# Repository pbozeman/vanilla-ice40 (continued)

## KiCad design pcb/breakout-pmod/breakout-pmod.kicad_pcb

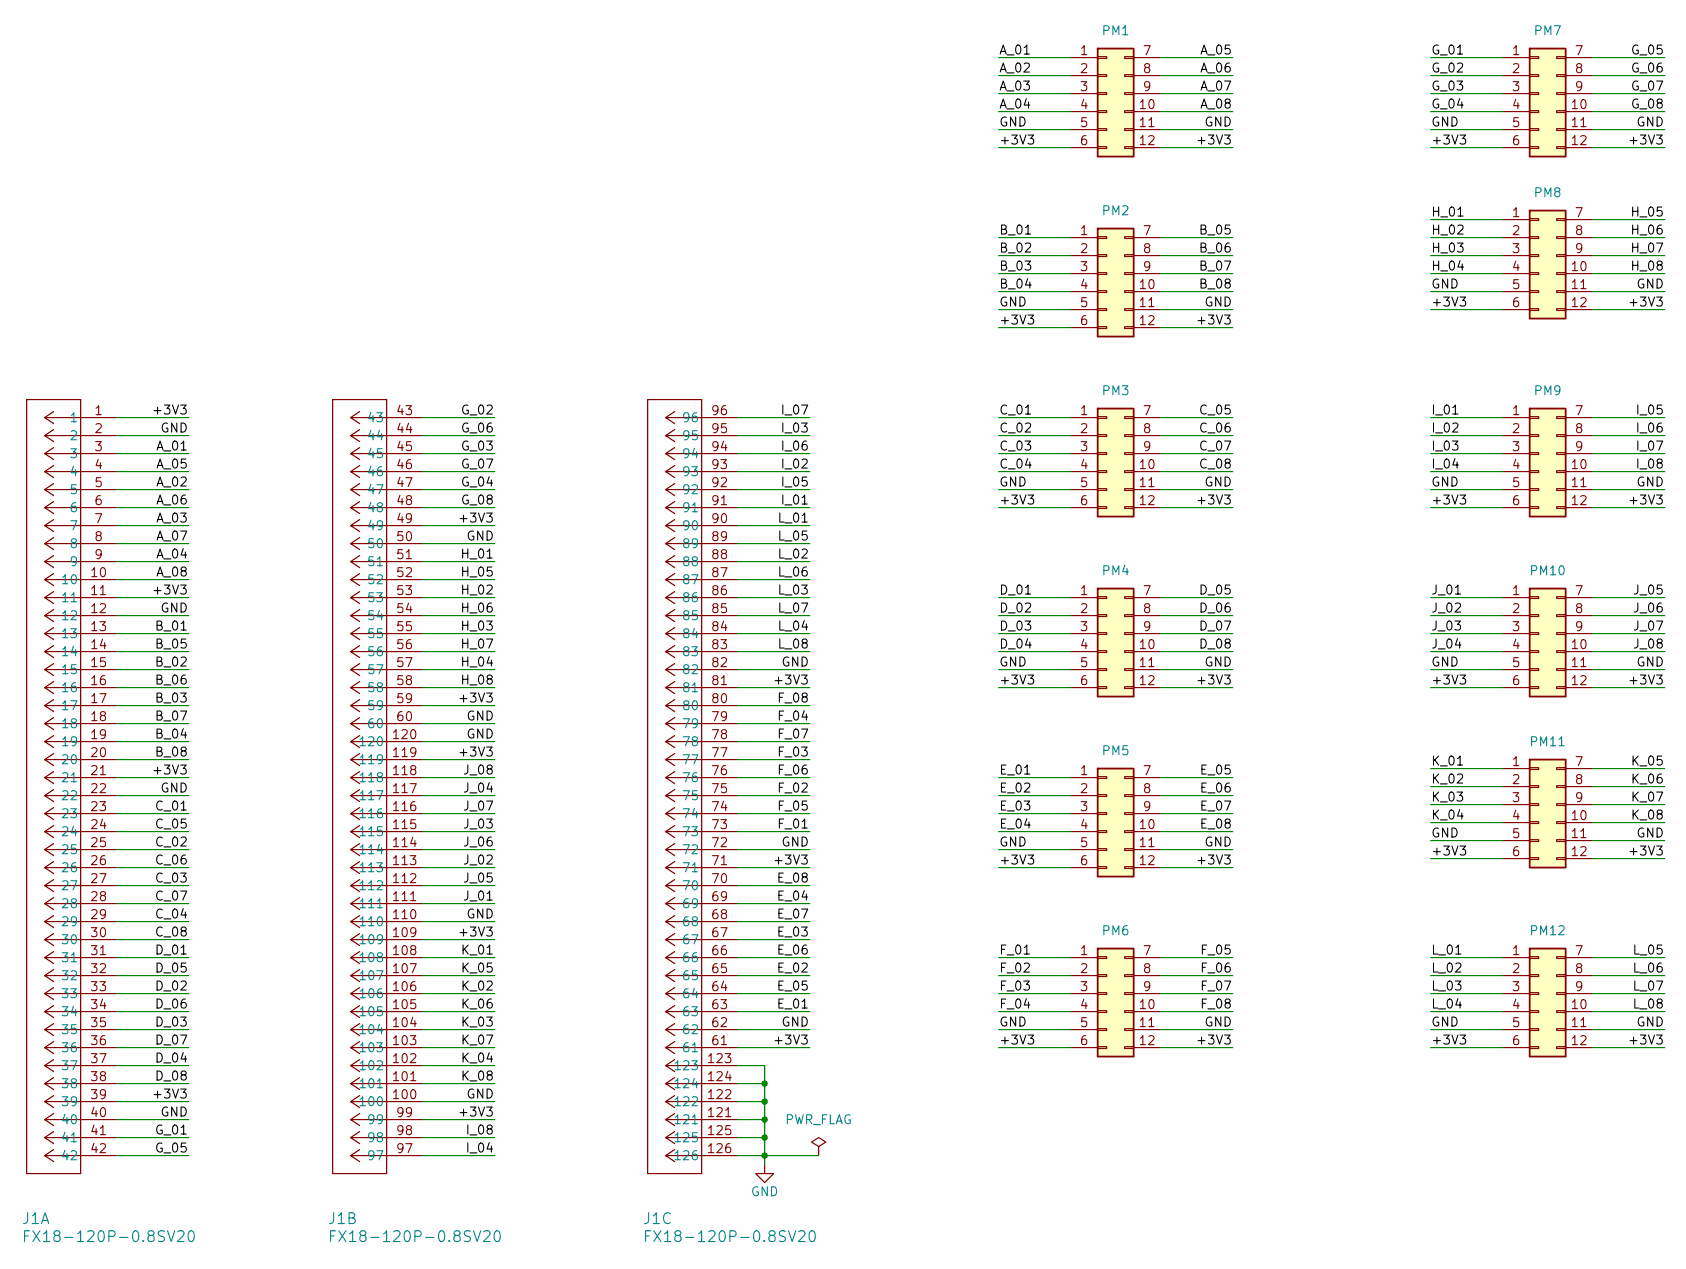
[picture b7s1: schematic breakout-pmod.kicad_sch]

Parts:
J1: FX18-120P-0.8SV20; CUSTOM_FX_120P-0.8SH20; Digi-Key Part Number H11865-ND
PM1, PM2, PM3, PM4, PM5, PM6, PM7, PM8, PM9, PM10: Conn_02x06_Top_Bottom; PMOD_12p_Horizontal; Digi-Key Part Number S5559-ND
PM11, PM12: Conn_02x06_Top_Bottom; PMOD_12p_Horizontal; Digi-Key Part Number S7109-ND

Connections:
/+3V3: J1.1, J1.11, J1.21, J1.39, J1.49, J1.59, J1.61, J1.71, J1.81, J1.99, J1.109, J1.119, PM1.6, PM1.12, PM2.6, PM2.12, PM3.6, PM3.12, PM4.6, PM4.12, PM5.6, PM5.12, PM6.6, PM6.12, PM7.6, PM7.12, PM8.6, PM8.12, PM9.6, PM9.12, PM10.6, PM10.12, PM11.6, PM11.12, PM12.6, PM12.12
/A_01: J1.3, PM1.1
/A_02: J1.5, PM1.2
/A_03: J1.7, PM1.3
/A_04: J1.9, PM1.4
/A_05: J1.4, PM1.7
/A_06: J1.6, PM1.8
/A_07: J1.8, PM1.9
/A_08: J1.10, PM1.10
/B_01: J1.13, PM2.1
/B_02: J1.15, PM2.2
/B_03: J1.17, PM2.3
/B_04: J1.19, PM2.4
/B_05: J1.14, PM2.7
/B_06: J1.16, PM2.8
/B_07: J1.18, PM2.9
/B_08: J1.20, PM2.10
/C_01: J1.23, PM3.1
/C_02: J1.25, PM3.2
/C_03: J1.27, PM3.3
/C_04: J1.29, PM3.4
/C_05: J1.24, PM3.7
/C_06: J1.26, PM3.8
/C_07: J1.28, PM3.9
/C_08: J1.30, PM3.10
/D_01: J1.31, PM4.1
/D_02: J1.33, PM4.2
/D_03: J1.35, PM4.3
/D_04: J1.37, PM4.4
/D_05: J1.32, PM4.7
/D_06: J1.34, PM4.8
/D_07: J1.36, PM4.9
/D_08: J1.38, PM4.10
/E_01: J1.63, PM5.1
/E_02: J1.65, PM5.2
/E_03: J1.67, PM5.3
/E_04: J1.69, PM5.4
/E_05: J1.64, PM5.7
/E_06: J1.66, PM5.8
/E_07: J1.68, PM5.9
/E_08: J1.70, PM5.10
/F_01: J1.73, PM6.1
/F_02: J1.75, PM6.2
/F_03: J1.77, PM6.3
/F_04: J1.79, PM6.4
/F_05: J1.74, PM6.7
/F_06: J1.76, PM6.8
/F_07: J1.78, PM6.9
/F_08: J1.80, PM6.10
/G_01: J1.41, PM7.1
/G_02: J1.43, PM7.2
/G_03: J1.45, PM7.3
/G_04: J1.47, PM7.4
/G_05: J1.42, PM7.7
/G_06: J1.44, PM7.8
/G_07: J1.46, PM7.9
/G_08: J1.48, PM7.10
/H_01: J1.51, PM8.1
/H_02: J1.53, PM8.2
/H_03: J1.55, PM8.3
/H_04: J1.57, PM8.4
/H_05: J1.52, PM8.7
/H_06: J1.54, PM8.8
/H_07: J1.56, PM8.9
/H_08: J1.58, PM8.10
/I_01: J1.91, PM9.1
/I_02: J1.93, PM9.2
/I_03: J1.95, PM9.3
/I_04: J1.97, PM9.4
/I_05: J1.92, PM9.7
/I_06: J1.94, PM9.8
/I_07: J1.96, PM9.9
/I_08: J1.98, PM9.10
/J_01: J1.111, PM10.1
/J_02: J1.113, PM10.2
/J_03: J1.115, PM10.3
/J_04: J1.117, PM10.4
/J_05: J1.112, PM10.7
/J_06: J1.114, PM10.8
/J_07: J1.116, PM10.9
/J_08: J1.118, PM10.10
/K_01: J1.108, PM11.1
/K_02: J1.106, PM11.2
/K_03: J1.104, PM11.3
/K_04: J1.102, PM11.4
/K_05: J1.107, PM11.7
/K_06: J1.105, PM11.8
/K_07: J1.103, PM11.9
/K_08: J1.101, PM11.10
/L_01: J1.90, PM12.1
/L_02: J1.88, PM12.2
/L_03: J1.86, PM12.3
/L_04: J1.84, PM12.4
/L_05: J1.89, PM12.7
/L_06: J1.87, PM12.8
/L_07: J1.85, PM12.9
/L_08: J1.83, PM12.10
GND: J1.2, J1.12, J1.22, J1.40, J1.50, J1.60, J1.62, J1.72, J1.82, J1.100, J1.110, J1.120, J1.121, J1.122, J1.123, J1.124, J1.125, J1.126, PM1.5, PM1.11, PM2.5, PM2.11, PM3.5, PM3.11, PM4.5, PM4.11, PM5.5, PM5.11, PM6.5, PM6.11, PM7.5, PM7.11, PM8.5, PM8.11, PM9.5, PM9.11, PM10.5, PM10.11, PM11.5, PM11.11, PM12.5, PM12.11

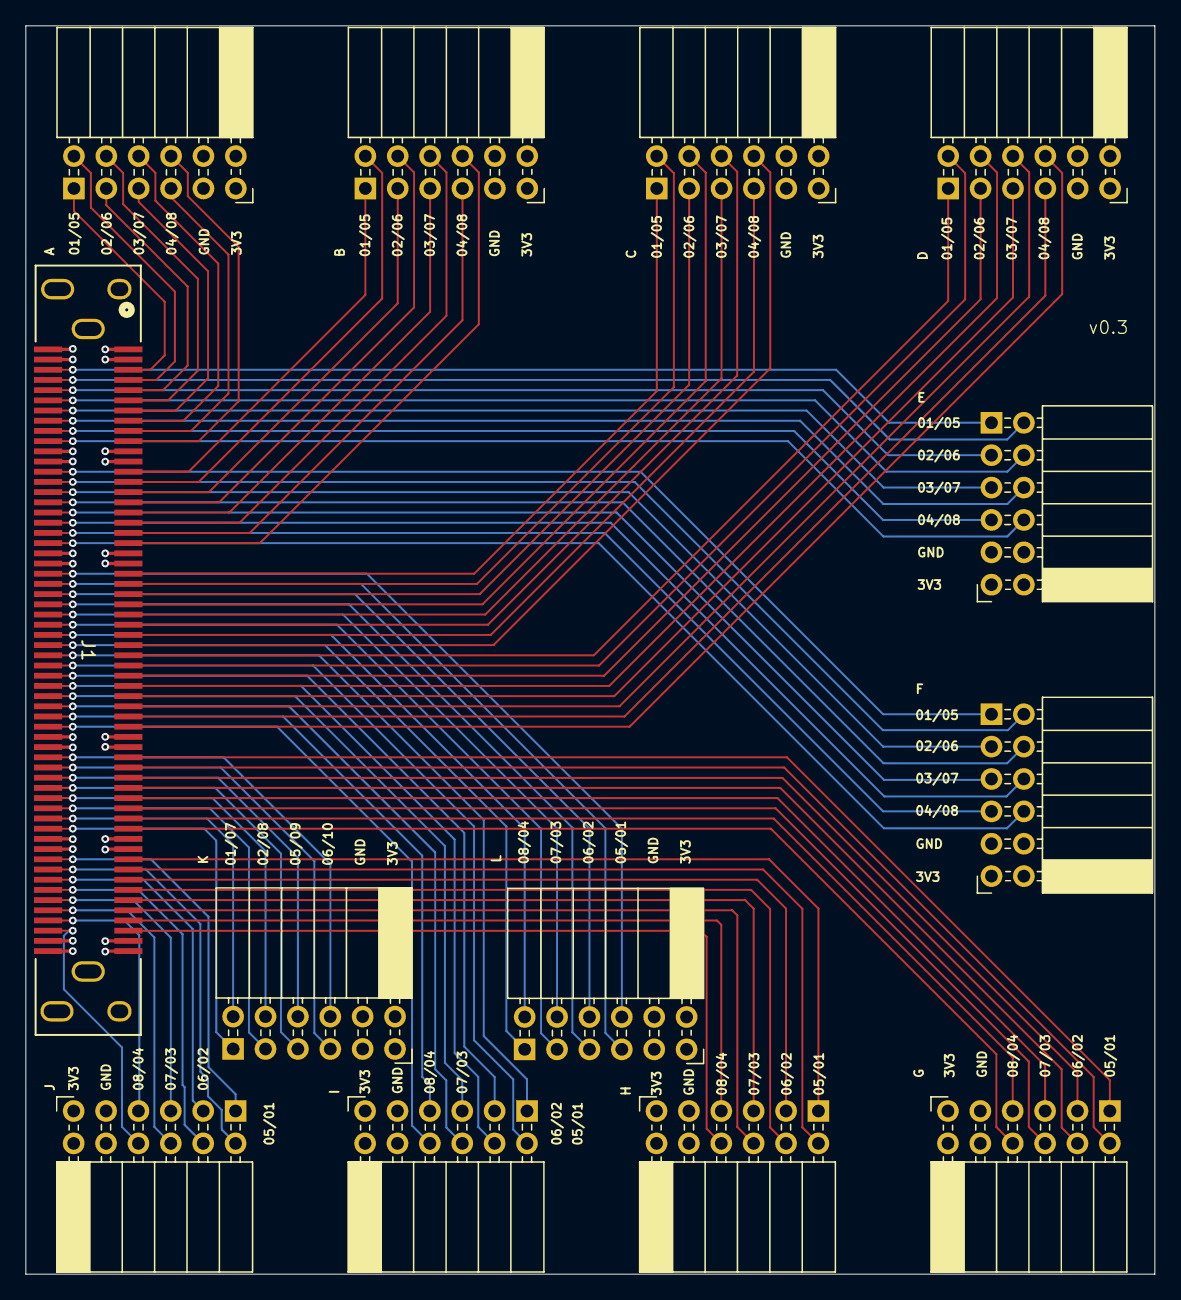
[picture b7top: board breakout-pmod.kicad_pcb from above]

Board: 4 copper layers, 88.6 x 97.9 mm, 13 parts (0 on the bottom side), 98 nets.

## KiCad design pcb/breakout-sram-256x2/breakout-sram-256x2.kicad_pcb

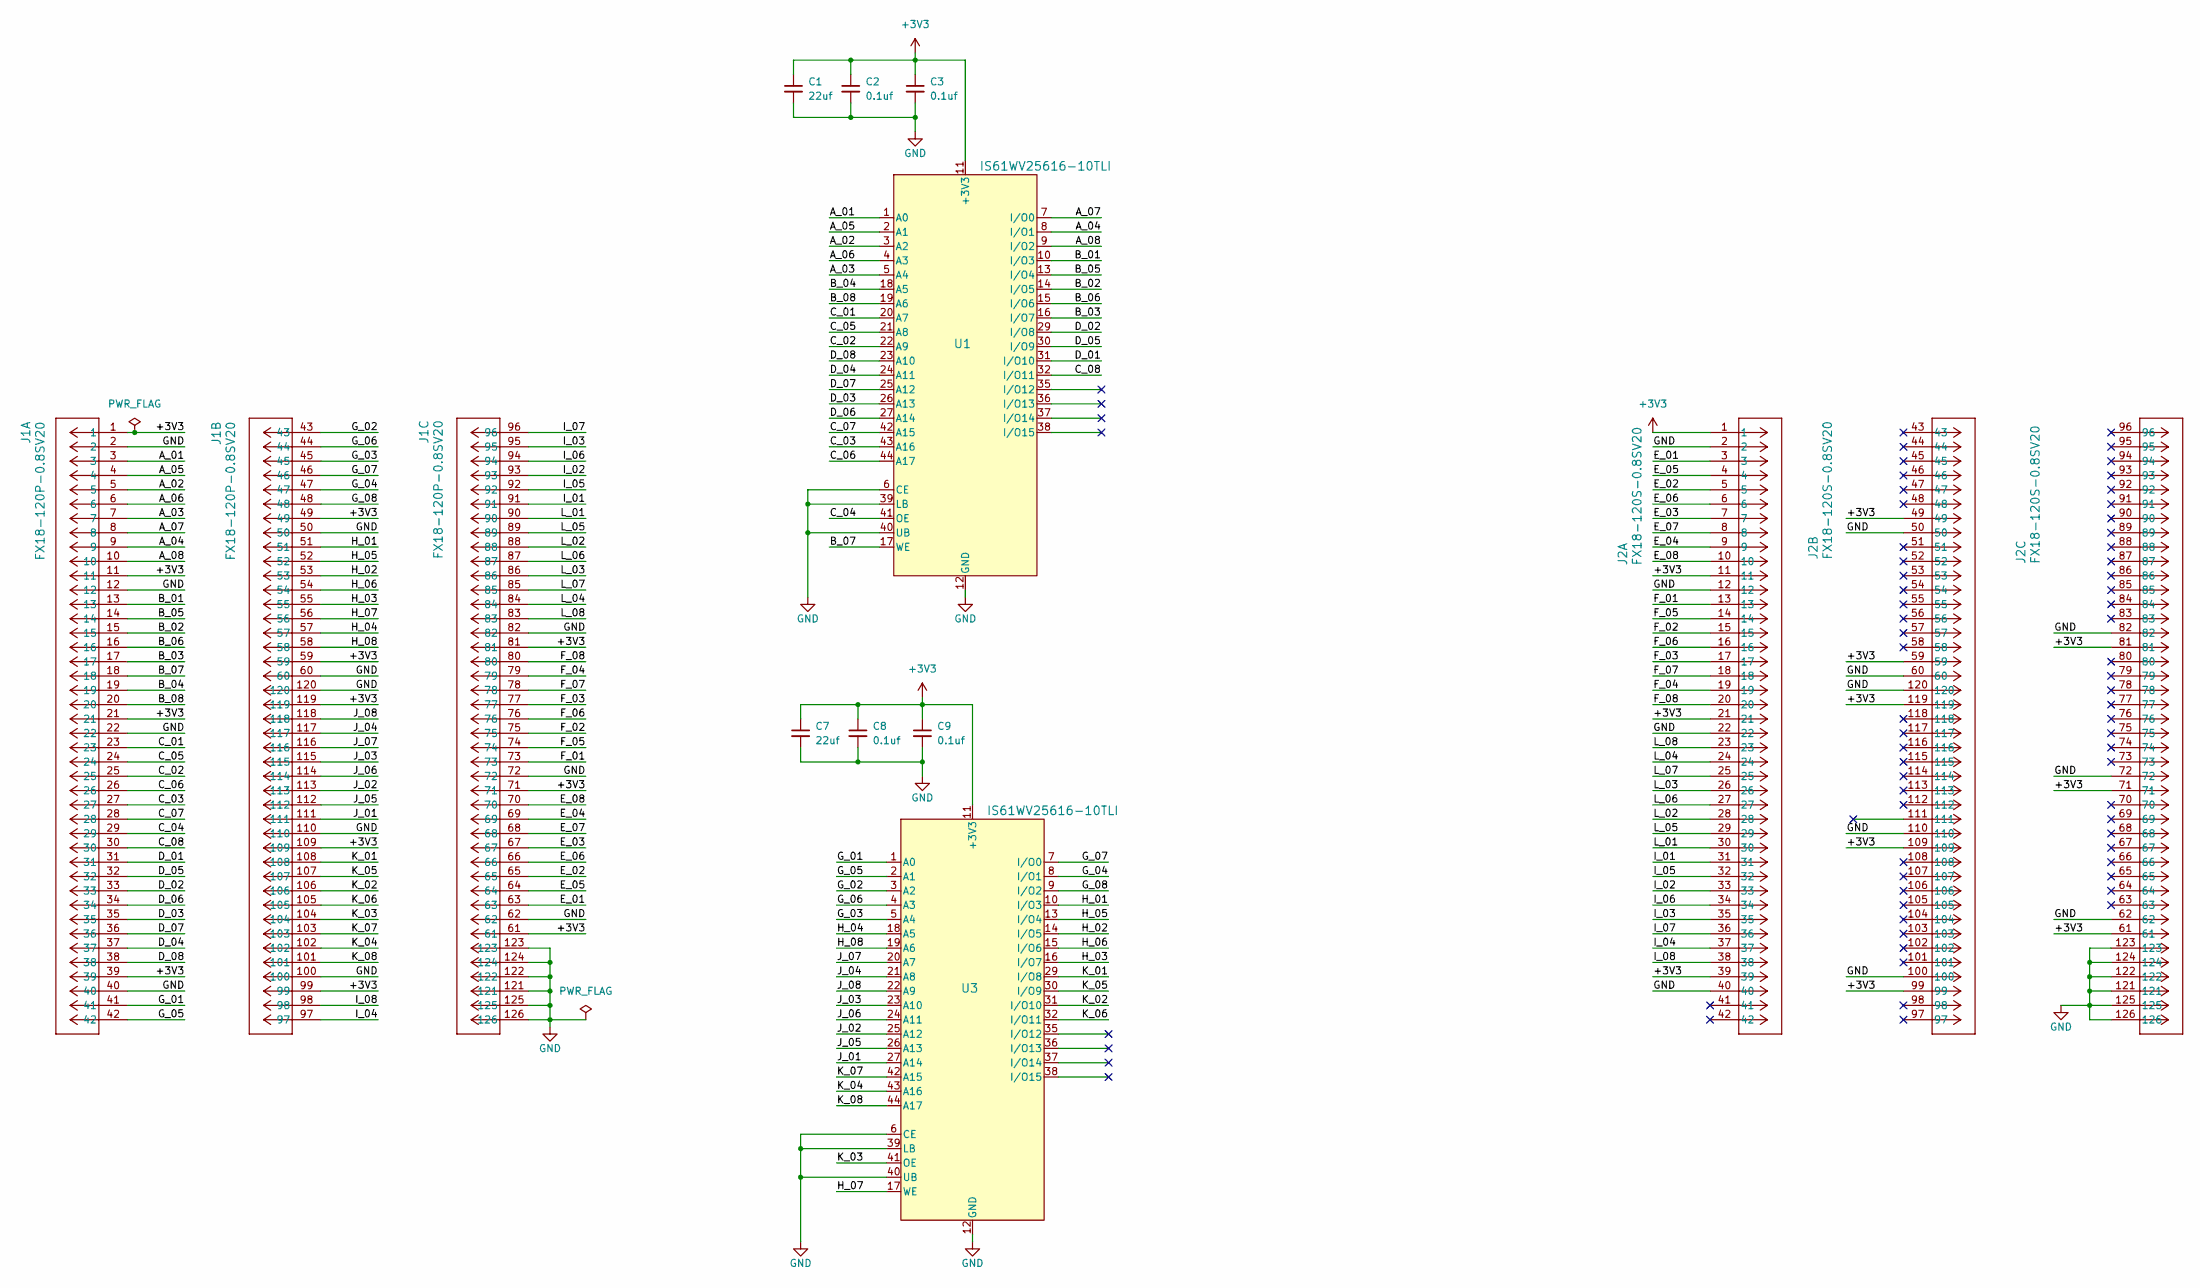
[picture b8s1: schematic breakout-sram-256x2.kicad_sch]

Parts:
C1, C7: 22uf; C_0603_1608Metric; LCSC Part # C59461
C2, C3, C8, C9: 0.1uf; C_0402_1005Metric; LCSC Part # C1525
J1: FX18-120P-0.8SV20; CUSTOM_FX_120P-0.8SH20; Digi-Key Part Number H11865-ND
J2: FX18-120S-0.8SV20; CUSTOM_FX_120S-0.8SH20; Digi-Key Part Number H11867-ND
U1, U3: IS61WV25616-10TLI; 44L_TSOP-2_400_ISI; LCSC Part # C883296

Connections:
+3V3: C1.1, C2.1, C3.1, C7.1, C8.1, C9.1, J1.1, J1.11, J1.21, J1.39, J1.49, J1.59, J1.61, J1.71, J1.81, J1.99, J1.109, J1.119, J2.1, J2.11, J2.21, J2.39, J2.49, J2.59, J2.61, J2.71, J2.81, J2.99, J2.109, J2.119, U1.11 (+3V3), U1.33 (+3V3), U3.11 (+3V3), U3.33 (+3V3)
/A_01: J1.3, U1.1 (A0)
/A_02: J1.5, U1.3 (A2)
/A_03: J1.7, U1.5 (A4)
/A_04: J1.9, U1.8 (I/O1)
/A_05: J1.4, U1.2 (A1)
/A_06: J1.6, U1.4 (A3)
/A_07: J1.8, U1.7 (I/O0)
/A_08: J1.10, U1.9 (I/O2)
/B_01: J1.13, U1.10 (I/O3)
/B_02: J1.15, U1.14 (I/O5)
/B_03: J1.17, U1.16 (I/O7)
/B_04: J1.19, U1.18 (A5)
/B_05: J1.14, U1.13 (I/O4)
/B_06: J1.16, U1.15 (I/O6)
/B_07: J1.18, U1.17 (WE)
/B_08: J1.20, U1.19 (A6)
/C_01: J1.23, U1.20 (A7)
/C_02: J1.25, U1.22 (A9)
/C_03: J1.27, U1.43 (A16)
/C_04: J1.29, U1.41 (OE)
/C_05: J1.24, U1.21 (A8)
/C_06: J1.26, U1.44 (A17)
/C_07: J1.28, U1.42 (A15)
/C_08: J1.30, U1.32 (I/O11)
/D_01: J1.31, U1.31 (I/O10)
/D_02: J1.33, U1.29 (I/O8)
/D_03: J1.35, U1.26 (A13)
/D_04: J1.37, U1.24 (A11)
/D_05: J1.32, U1.30 (I/O9)
/D_06: J1.34, U1.27 (A14)
/D_07: J1.36, U1.25 (A12)
/D_08: J1.38, U1.23 (A10)
/E_01: J1.63, J2.3
/E_02: J1.65, J2.5
/E_03: J1.67, J2.7
/E_04: J1.69, J2.9
/E_05: J1.64, J2.4
/E_06: J1.66, J2.6
/E_07: J1.68, J2.8
/E_08: J1.70, J2.10
/F_01: J1.73, J2.13
/F_02: J1.75, J2.15
/F_03: J1.77, J2.17
/F_04: J1.79, J2.19
/F_05: J1.74, J2.14
/F_06: J1.76, J2.16
/F_07: J1.78, J2.18
/F_08: J1.80, J2.20
/G_01: J1.41, U3.1 (A0)
/G_02: J1.43, U3.3 (A2)
/G_03: J1.45, U3.5 (A4)
/G_04: J1.47, U3.8 (I/O1)
/G_05: J1.42, U3.2 (A1)
/G_06: J1.44, U3.4 (A3)
/G_07: J1.46, U3.7 (I/O0)
/G_08: J1.48, U3.9 (I/O2)
/H_01: J1.51, U3.10 (I/O3)
/H_02: J1.53, U3.14 (I/O5)
/H_03: J1.55, U3.16 (I/O7)
/H_04: J1.57, U3.18 (A5)
/H_05: J1.52, U3.13 (I/O4)
/H_06: J1.54, U3.15 (I/O6)
/H_07: J1.56, U3.17 (WE)
/H_08: J1.58, U3.19 (A6)
/I_01: J1.91, J2.31
/I_02: J1.93, J2.33
/I_03: J1.95, J2.35
/I_04: J1.97, J2.37
/I_05: J1.92, J2.32
/I_06: J1.94, J2.34
/I_07: J1.96, J2.36
/I_08: J1.98, J2.38
/J_01: J1.111, U3.27 (A14)
/J_02: J1.113, U3.25 (A12)
/J_03: J1.115, U3.23 (A10)
/J_04: J1.117, U3.21 (A8)
/J_05: J1.112, U3.26 (A13)
/J_06: J1.114, U3.24 (A11)
/J_07: J1.116, U3.20 (A7)
/J_08: J1.118, U3.22 (A9)
/K_01: J1.108, U3.29 (I/O8)
/K_02: J1.106, U3.31 (I/O10)
/K_03: J1.104, U3.41 (OE)
/K_04: J1.102, U3.43 (A16)
/K_05: J1.107, U3.30 (I/O9)
/K_06: J1.105, U3.32 (I/O11)
/K_07: J1.103, U3.42 (A15)
/K_08: J1.101, U3.44 (A17)
/L_01: J1.90, J2.30
/L_02: J1.88, J2.28
/L_03: J1.86, J2.26
/L_04: J1.84, J2.24
/L_05: J1.89, J2.29
/L_06: J1.87, J2.27
/L_07: J1.85, J2.25
/L_08: J1.83, J2.23
GND: C1.2, C2.2, C3.2, C7.2, C8.2, C9.2, J1.2, J1.12, J1.22, J1.40, J1.50, J1.60, J1.62, J1.72, J1.82, J1.100, J1.110, J1.120, J1.121, J1.122, J1.123, J1.124, J1.125, J1.126, J2.2, J2.12, J2.22, J2.40, J2.50, J2.60, J2.62, J2.72, J2.82, J2.100, J2.110, J2.120, J2.121, J2.122, J2.123, J2.124, J2.125, J2.126, U1.6 (CE), U1.12 (GND), U1.34 (GND), U1.39 (LB), U1.40 (UB), U3.6 (CE), U3.12 (GND), U3.34 (GND), U3.39 (LB), U3.40 (UB)

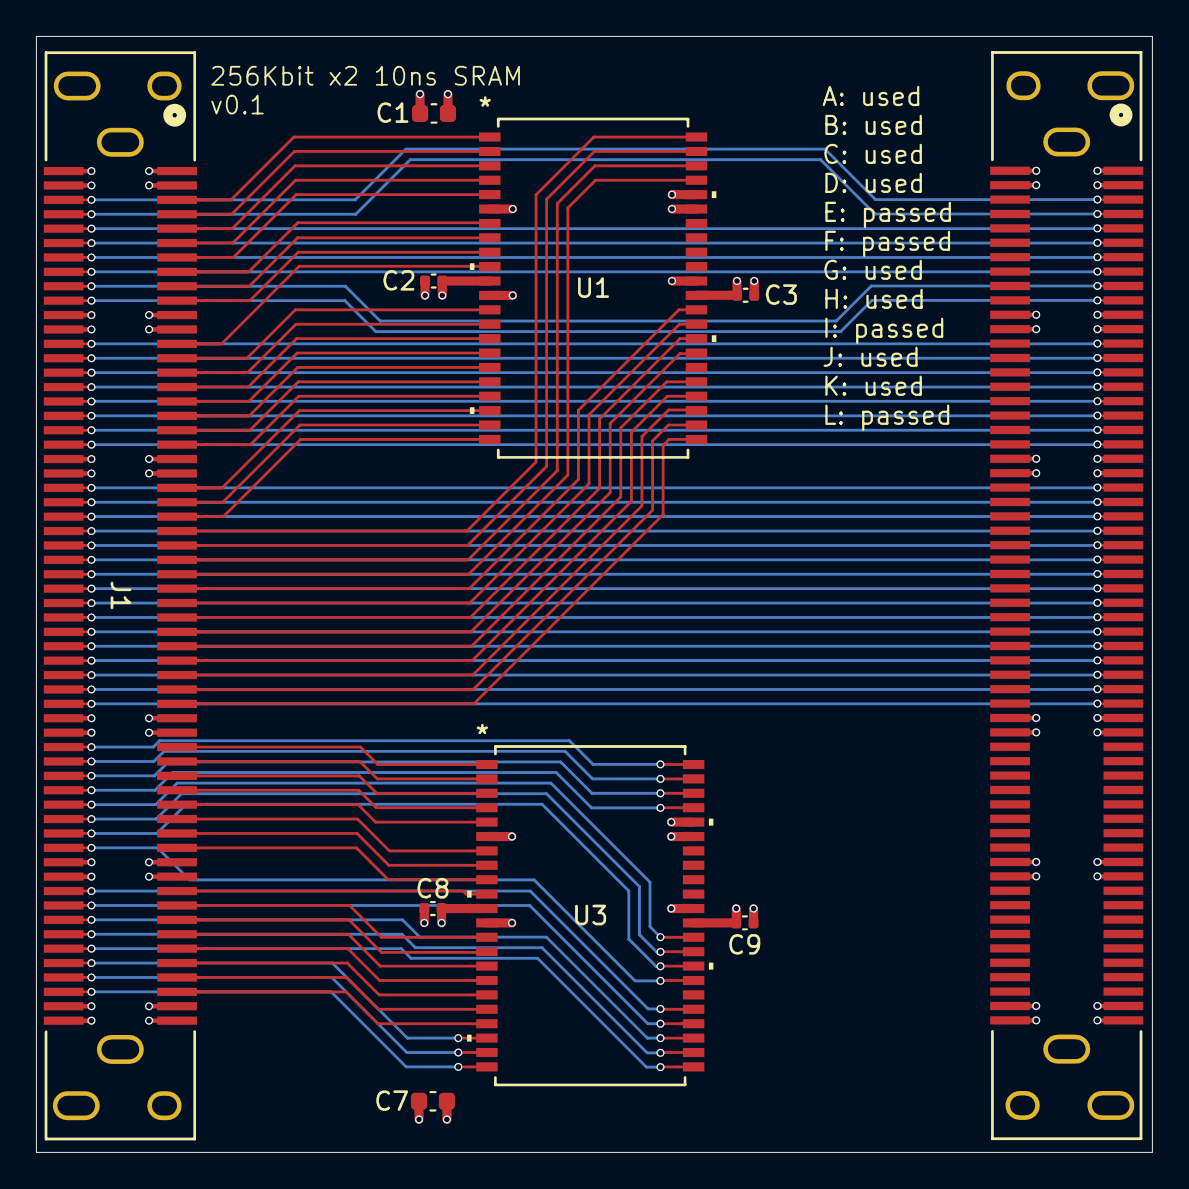
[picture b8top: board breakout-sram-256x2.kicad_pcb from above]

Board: 4 copper layers, 62.0 x 62.0 mm, 10 parts (0 on the bottom side), 98 nets.

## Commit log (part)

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2024-11-13 [sync_fifo] this will replace fifo.sv
2024-11-13 [sync_fifo] whitespace fix via fmt
2024-11-14 [axi3_to2] factor out arbiter logic
2024-11-14 [sticky_bit] sticky bit implementation
2024-11-14 [axi3_to_2] out0 read channel
2024-11-14 [axi_3to2] replace txn_done with sticky_bit
    also, delete txn_done, since it can be so easily implemented with
    sticky_bit
2024-11-15 [fixme][axi_3to2] fixme note about wasting half the sub device capacity
2024-11-16 [axi_3to2] fix sequential write
    TODO: fixing this introduced a 1 cycle bubble that we were trying to
    avoid. This will likely need to be revisited, but at least this is
    functionally correct.
2024-11-18 [gfx] use axi like signaling for gfx_ modules
2024-11-19 [makefile] nextpnr custom seed infra
2024-11-20 [vga] remove likely incorrect comment from pixel stream
    I didn't realize initially how wildly varied fmax was coming out of
    nextpnr with small/inconsequential logic tweaks at the time the comment
    was written.
2024-11-21 [sync_fifo] clean up tb
2024-11-21 [vga] use sync_fifo in pixel_stream
    This fixed some bugs with extended pixels at the end of a line.
    Also started a tb for vga_fb_pixel_stream to validate vga timing.
    TODO: The nextpnr timings in everything that uses pixels_stream got
    a lot more finicky and more explicit seeds were needed. Look at timing
    in icecube2 and figure out what to pipeline to give more breathing room.
2024-11-21 [gfx][fb][vga] remove default params to modules in lib
    This prevents an accidental mismatch if one is left out.
2024-11-21 [gfx] gfx_vga linear write test
2024-11-22 [gfx] gfx_vga even write test
2024-11-22 [gfx_vga_3to2] prioritize the display
2024-11-22 [scripts] increase max seed in find seed
2024-11-22 [adc] revive adc_xy_vga
    The output is glitchy, just like the 3to2 version.
    However, commit 106331ad was not.
2024-11-24 [flake] explicitly add python rather than the system version
    This provides the infra for adding extra python packages
2024-11-24 [makefile] extract prn command
2024-11-24 [makefile][flake] auto-determine and cache nextprn seeds
    Added flock to serialize locking. I didn't see a way to
    do this with .NOTPARALLEL in make because each of the
    seeds was it's own rule.
2024-11-24 [makefile] move seeds to target specific bits dir
2024-11-25 [adc] bump adc cdc addr size. fixes vga glitch
2024-11-25 [lattice][adc_3to2] add lattice project
2024-11-26 [makefile] enable tops that can't meet timing
2024-11-26 [adc] rename x/y_bus to x/y_io
2024-11-29 [vga] remove stale signal
2024-11-29 [axi_3to2] remove redundant conditional
2024-11-29 [sync_fifo] add w_almost_full
2024-11-29 [adc] remove stale frame tracking
    This is going to move to vga fade.
2024-11-29 [adc][gfx] rm 3to2 modules
    I originally thought these would be used for fading, but fading
    is only going to use the 2 to 1 fb writer going forward.
2024-11-29 [gfx] delete stale debugging line from fade
2024-11-29 [vga] don't split out rgb in pixel stream output
    This will let the caller pack more info into the pixel data.
    TODO: this should have been called data instead of color.
2024-11-30 [adc] clear screen fully before starting
2024-11-30 [vga] fade pixels rather than blanking them
2024-12-02 [env] set gtk theme to dark
    gtkwave was burning my eyes. This also needs --dark on the command line,
    otherwise, the 'Signals' section remains white. I couldn't figure out
    how to get direnv to pass an alias or function to the env, so I made an
    alias in my main nix-config instead.
2024-12-02 [sram_test] use sticky bit in axi_sram_tester
    This is prep for some controller speeds ups
2024-12-02 [sram_test] remove READ_WAIT state
    This is in prep for controller speedup
2024-12-04 [fifo] rm old fifo
2024-12-04 [makefile] add -Wno-PINCONNECTEMPTY
    Will start doing .signal() during module instantiating instead of having
    to pass in an unused signal and set a pragma.
2024-12-04 [axi_sram] remove a cycle of latency between back to back ios
2024-12-04 [axi_arbiter] start of parameterized arbiter
2024-12-04 [axi_arbiter] clarify comment re back to back grants for a single M
2024-12-04 [axi_arbiter] rename the axi_arbitrated_mux to axi_arbiter
2024-12-05 [arbiter] reduce fifo size, avoid overrun, and add ltp comment
2024-12-05 [makefile] add a flock timeout for seed finding
2024-12-05 [axi_sram] add spec mismatch comment
2024-12-05 [vga_stripe] duplicate vga in prep for stripe perf testing
2024-12-05 [lib] rename counter to counter_fixed
2024-12-05 [lib] rename iter to iter_fixed
2024-12-07 [iter] redo with dyamic max
2024-12-08 [axi] read_words
2024-12-09 [sync_fifo] add simul test
2024-12-10 [makefile] disable tlight while working on higher resolutions
2024-12-10 [axi] fix include guard on stripe reader
2024-12-10 [axi] rename read_words to readn
2024-12-11 [axi] axi_stripe_router
2024-12-11 [axi][sram] drop sram_ prefix from gfx/vga axi signals
2024-12-11 [vga] use new iter in vga_pixel_addr
2024-12-11 [vga] unify naming with gfx (col/row -> x/y)
2024-12-11 [vga] return x/y last from pixel_addr
2024-12-12 [vga] rename pixel_addr to pixel_iter
2024-12-12 [vga] pixel stream striped
2024-12-12 [axi] in readn only reset iter when inc
2024-12-12 [vga] only return non-vis pixels when enabled
2024-12-13 [gfx_vga_stripe] switch to use non-interconnect striping
2024-12-13 [tlight] disable when not 640x480
2024-12-13 [gfx] add some casts that were needed for 1024x768
2024-12-13 [makefile] remove comments re higher resolutions
2024-12-13 [adc] striped version
    Unsurprisingly, this doesn't pass nextpnr timing as it has a ltp of
    400. Will try on icecube2 and also try introducing skid buffers
    to break up the axi combinatorial paths.
2024-12-15 [axi][sb] skidbuffer demo
2024-12-15 [axi][sb] full axi-lite skidbuf
2024-12-15 [gfx] use skidbuffer in fade stripe
    nextpnr still can't meet timing
2024-12-15 [lattice][adc] use fade stripe
2024-12-15 [tb][sram] allow sram addr and data changes during reset
    This can happen during the stripe and readn oriented tests
    and gets triggered if we remove the reset from the sram_io_ice40,
    which is coming in a separate commit.
2024-12-15 [lattice] bump resolution to 800x600
2024-12-16 [sram] delete old sram_controller
2024-12-16 [gfx] remove gfx_vsync from non dbuf modules
2024-12-16 [axi][sb] simply axis skidbuf
2024-12-16 [vga] logic fixes in pixel stream striped
2024-12-17 [gfx][vga] speed up vga tests
    The corner cases are covered by other tbs and these just slow down the
    test suite.
    This reverts commit aa32c281f93ff0e1ed3e655f44baf4b3f023d300.
2024-12-17 [axi] remove stale tb comment
2024-12-18 [axi] fix stripe routing
2024-12-18 [sram][pcb] copy old sram to 256x4
2024-12-18 [sram][pcb] add footprint for 256x4
2024-12-18 [sram][pcb] rough footprint placement
2024-12-19 [sram][pcb] rename 256x4 -> 256x2
2024-12-19 [axi][sram] more robust ready check
2024-12-19 [axi][sram] populate 256x2 part numbers
2024-12-19 [pmod][pcb] remove top and bottom gnd pour
2024-12-19 [axi][adc] add jitter to adc tests. fix readn fifo overflow bug they trigger
2024-12-19 [makefile] don't run slow tests on quick make
2024-12-19 [git] ignore .DS_Store
2024-12-20 [gfx] disable gfx_demo_dbuf test
    It was a slow test already, so it wasn't getting run frequently, but it
    fails. I'm not sure if there is really a bug there or not, or if things
    changed around it and it atrophied, but I don't want to sort it out now
    while deep in other slow testing of the adc blanking.
2024-12-20 [adc] pull cdc fifo into axi version and manage it correctly
2024-12-20 [adc][gfx] 25mhz adc sampling clock with 2x stripe, no pixel drop
    Timing with icecube2 tbd.
2024-12-20 [adc] use pll for adc clk
2024-12-20 [lib] minor iter timing optimization
2024-12-21 [tlight] avoid make dep error when tlight has no deps
    See the comment in tlight_top.sv
2024-12-22 [adc][test] disable adc_xy_vga_fade at higher resolutions
    It needs more memory bandwidth than a single sram.
2024-12-22 [test] reduce adc sample rate at higher resolution
2024-12-22 [axi] standardize axi port names for stripe writer
2024-12-22 [axi] fifobuf_write
2024-12-22 [gfx][test] bump adc sample rate at 800x600 back to 20msps
    The fifo stripe writer let's us get full bw on the sram.
2024-12-22 [test][axi] clear arvalid in stripe readn test
2024-12-23 [test][gfx] wider lines in fade stripe test
    This pushes the prefetcher harder
2024-12-23 [pins] add sram 256x2 board to pins and regen constraints files
2024-12-23 [test][gfx] turn down line len on vga stripe test
2024-12-23 [adc] initial x4 sram file
    icecube2 synthesis and programming tbd
2024-12-23 [gfx] register the read side of the fade fifo
    The sync_fifo is fwft and this is needed to meet timing in icecube2
2024-12-24 [test][adc] tweak stripe tb adc rates
    We don't get the theoretical max and can't run right at the edges.
    This might get fixed, but might be ok, it's tbd.
2025-02-22 [pcb] add DF40C-100DS-0-4V-51 models
2025-02-24 [hx8k][pcb] route new connector on lower right
2025-02-24 [pcb] add DF40C-40DS models
2025-02-25 [hx8k][pcb] fixed footprint for new conn to be path relative
2025-02-25 [hx8k][pcb] updated J refs
2025-02-25 [hx8k][pcb] switch to ComponentEngine DF40C footprints
2025-02-26 [sram_x4][pcb] stackable 4x sram
2025-02-27 [adc][pcb] stackable version
2025-02-27 [pcb] jclcpb exports for v1.5 stackable boards
2025-04-13 [adc][sram] fix part numbers for plugs
2025-05-03 [hx8k][pcb] fixme note for power switch and minor silk fixes
2025-05-03 [scripts] add pins_v2
2025-05-03 [scripts][pins] go all the way to physical pin in v2
2025-05-07 [sram_4x][pcb] pull in traces and edge cut for more clearance
2025-05-07 [pcb][hx4k] start of move to samtec connectors
2025-05-07 [pcb][hx4k] clean up old post escape config traces
2025-05-08 [pcb][hx4k] start of via changes
2025-05-08 [pcb][hx8k] new IOT escape
2025-05-08 [pcb][hx8k] better IOR routing
2025-05-08 [pcb][hx8k] bga gnd fills
2025-05-08 [pcb][hx8k] moved and rotated
2025-05-08 [pcb][hx8k] initial top side IOT header assignment
2025-05-09 [pcb][hx8k] fixed IOT initial assigmenments
2025-05-09 [pcb][hx8k] IOB assigned
2025-05-10 [hx8k][pcb] start of rough layout
2025-05-10 [hx8k][pcb] alignment marks for io tracks
2025-05-11 [hx8k][pcb] j1 and j2 top layer initial routing
2025-05-12 [hx8k][pcb] j1 and j2 mirroring fixed
2025-05-12 [hx8k][pcb] prep for move to 8 layers
2025-05-13 [hx8k][pcb] redo escape for 8 layer
2025-05-13 [hx8k][pcb] cleaned up initial DRC errors
2025-05-13 [hx8k][pcb] update QTH pad, bump in headers
2025-05-13 [hx8k][pcb] j1/j3 via cleanup
2025-05-13 [hx8k][pcb] header gnd pours
2025-05-13 [hx8k][pcb] j1 upper outside assigned
2025-05-13 [hx8k][pcb] j1 l1 grid prep
2025-05-14 [hx8k][pcb] L1 J1 redone for 8 layers with >3w spacing
2025-05-14 [hx8k][pcb] upper j1 sig2 traces
2025-05-14 [hx8k][pcb] add 3v3 pour
2025-05-17 [hx8k][pcb] j1 lower escape
2025-05-17 [hx8k][pcb] j1 l1 in progress
2025-05-17 [hx8k][pcb] lower j1 l1 routed
2025-05-18 [hx8k][pcb] 1v2 routing improvements
2025-05-18 [hx8k][pcb] upper j2 l1 routed
2025-05-18 [hx8k][pcb] minor net fixes
2025-05-18 [hx8k][pcb] upper j2 sig4 routed
2025-05-19 [hx8k][pcb] lower j2 guides placed
2025-05-19 [hx8k][pcb] lower j2 dual escape - not assigned
2025-05-19 [hx8k][pcb] j2 sig2 dual escape - not assigned
2025-05-20 [hx8k][pcb] j2 routed
2025-05-20 [hx8k][pcb] rough layout of full board
2025-05-21 [hx8k][pcb] move headers and banks to sheets
2025-05-22 [hx8k][pcb] move usb_c_power to use symbol lib
2025-05-22 [hx8k][pcb] completed all moves to lib other than ice40
2025-05-23 [hx8k][pcb] start of routing programmer
2025-05-23 [hx8k][pcb] working through final traces from hx8k
2025-05-28 [hx8k][pcb] finalize silks
2025-05-29 [pcb][leds] start of led shield
2025-05-30 [pcb][hx8k] add 3v3 to headers
2025-05-30 [pcb][leds] starting placement
2025-05-31 [pcb][leds] delete unused subsheet
2025-06-01 [pcb][sram-4x] all but pmod routed for adc board
    The sram is doing double duty here during the cross over. It supports
    the dfc stacking connector during the transition. It will be removed.
2025-06-05 [pcb] misc fixes during jlcpcb production submission
2025-06-08 [hx8k][pcb] part cleanup
2025-06-11 [scripts][pins] start v2_1 board
2025-06-11 [pcb][hx8k] add helper labels in header schematic
2025-06-13 [scripts][pins] hack in remaining bank headers
2025-06-14 [scripts][pins] add v2.1 pmods. work around D sram signal issue
2025-06-15 [scripts][pins] D bank pin bodge wire
2025-06-23 [sram] add 512x2
